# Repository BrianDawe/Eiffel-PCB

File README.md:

# Eiffel-PCB

This is my implementation of the Eiffel PS2 keyboard/mouse adapter for the Mega ST/TT computers

This repo contains the KiCAD project files and all gerbers needed to make the PCB's

The original Eiffel project was created by Didier Méquignon and can be found here https://didierm.pagesperso-orange.fr/eiffel-e.htm

The firmware can be downloaded from Didier's page.

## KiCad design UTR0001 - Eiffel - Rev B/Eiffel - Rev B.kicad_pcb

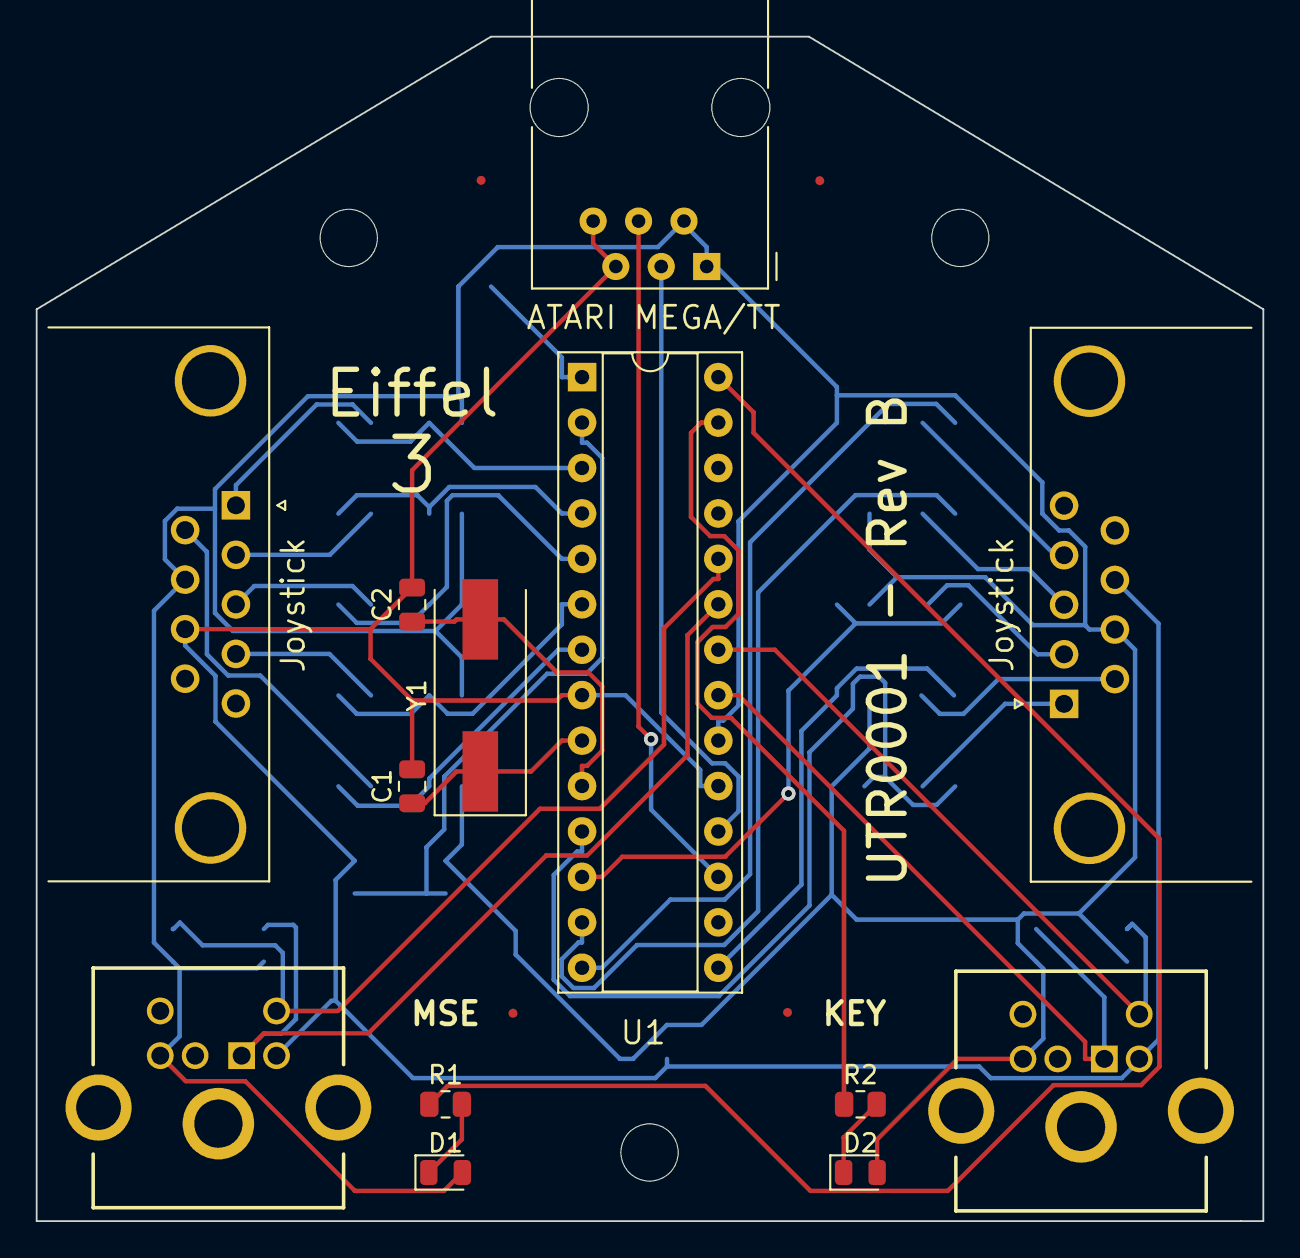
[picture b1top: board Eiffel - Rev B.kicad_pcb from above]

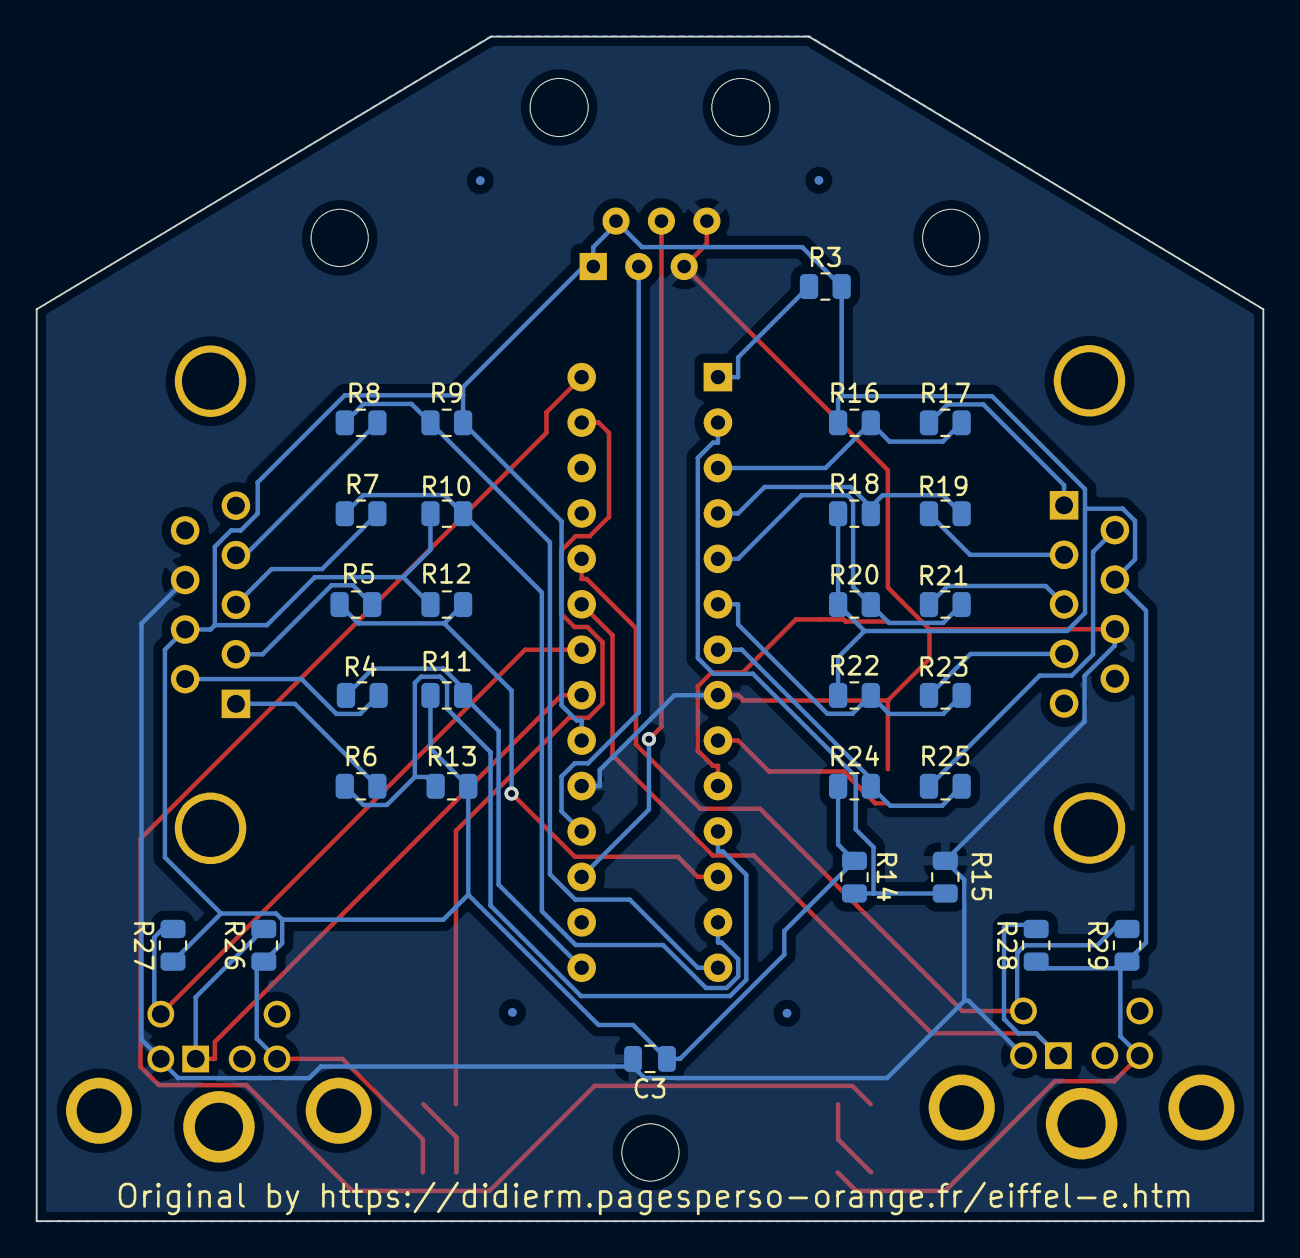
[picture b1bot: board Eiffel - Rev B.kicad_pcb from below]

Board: 2 copper layers, 68.6 x 66.2 mm, 41 parts (28 on the bottom side), 36 nets.

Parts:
ATARI MEGA/TT: 6P6C; RJ12_Amphenol_54601
C1, C2: 20pf; C_0805_2012Metric
C3: 0.1uF; C_0805_2012Metric
D1, D2: LED; LED_0805_2012Metric
Joystick: DB9_Male; DSUB-9_Male_Horizontal_P2.77x2.84mm_EdgePinOffset7.70mm_Hou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
Joystick#2: DB9_Male; DSUB-9_Male_Horizontal_P2.77x2.84mm_EdgePinOffset7.70mm_Hou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
KEY: Mini-DIN-6; MD60SM
MSE: Mini-DIN-6; MD60SM
R1, R2, R4, R5, R6, R7, R8, R17, R19, R21, R23, R25: 470R; R_0805_2012Metric
R3, R9, R10, R11, R12, R13, R14, R15, R16, R18, R20, R22, R24: 10K; R_0805_2012Metric
R26, R27, R28, R29: 10k; R_0805_2012Metric
U1: PIC16F876-XXISP; DIP-28_W7.62mm_Socket
Y1: 4MHz; Crystal_SMD_HC49-SD

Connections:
GND: ATARI MEGA/TT.5, ATARI MEGA/TT.6, C1.2, C2.2, C3.2, Joystick.8, Joystick#2.8, KEY.3, MSE.3, R15.2, U1.8 (VSS), U1.19 (VSS)
unnamed: C1.1, U1.9 (OSC1/CLKI), Y1.1
unnamed: C2.1, U1.10 (OSC2/CLKO), Y1.2
unnamed: ATARI MEGA/TT.1, ATARI MEGA/TT.2, C3.1, D1.2 (A), D2.2 (A), Joystick.7, Joystick#2.7, KEY.4, MSE.4, R3.1, R9.2, R10.2, R11.2, R12.2, R13.2, R14.1, R16.1, R18.1, R20.1, R22.1, R24.1, R26.1, R27.1, R28.1, R29.1, U1.20 (VDD)
unnamed: D1.1 (K), R1.2
unnamed: D2.1 (K), R2.2
unnamed: KEY.1, R26.2, U1.21 (INT/RB0)
unnamed: KEY.5, R27.2, U1.22 (RB1)
unnamed: MSE.1, R28.2, U1.23 (RB2)
unnamed: MSE.5, R29.2, U1.24 (PGM/RB3)
unnamed: Joystick#2.1, R6.2
unnamed: Joystick#2.2, R5.1
unnamed: Joystick#2.3, R7.1
unnamed: Joystick#2.4, R8.1
unnamed: Joystick#2.6, R4.1
unnamed: ATARI MEGA/TT.3, U1.18 (RC7/DT/RX)
unnamed: ATARI MEGA/TT.4, U1.17 (RC6/CK/TX)
unnamed: Joystick.1, R17.2
unnamed: Joystick.2, R19.2
unnamed: Joystick.3, R21.2
unnamed: Joystick.4, R23.2
unnamed: Joystick.6, R25.2
unnamed: R1.1, U1.28 (PGD/RB7)
unnamed: R2.1, U1.27 (PGC/RB6)
unnamed: R3.2, U1.1 (~MCLR/Vpp)
unnamed: R8.2, R9.1, U1.14 (RC3/SCK/SCL)
unnamed: R7.2, R10.1, U1.13 (RC2/CCP1)
unnamed: R4.2, R11.1, U1.15 (RC4/SDI/SDA)
unnamed: R5.2, R12.1, U1.12 (RC1/T1OSI/CCP2)
unnamed: R6.1, R13.1, U1.11 (RC0/T1OSO/T1CKI)
unnamed: R14.2, R15.1, U1.2 (AN0/RA0)
unnamed: R16.2, R17.1, U1.3 (AN1/RA1)
unnamed: R18.2, R19.1, U1.4 (Vref-/AN2/RA2)
unnamed: R20.2, R21.1, U1.5 (Vref+/AN3/RA3)
unnamed: R22.2, R23.1, U1.6 (T0CKI/RA4)
unnamed: R24.2, R25.1, U1.7 (~SS/AN4/RA5)
